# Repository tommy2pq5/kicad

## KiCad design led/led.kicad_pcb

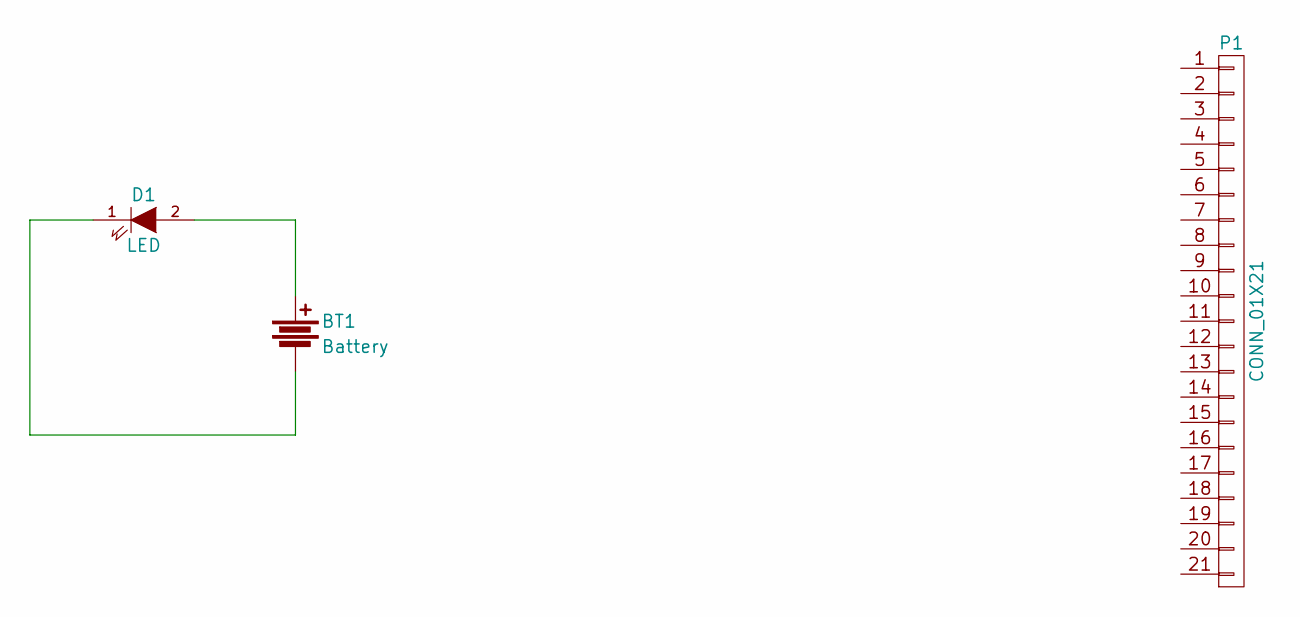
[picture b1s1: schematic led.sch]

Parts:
BT1: Battery; Pin_Header_Straight_2x01_Pitch2.54mm
D1: LED; LED_D5.0mm
P1: CONN_01X21; Pin_Header_Straight_1x21_Pitch2.54mm

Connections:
unnamed: BT1.1, D1.2 (A)
unnamed: BT1.2, D1.1 (K)

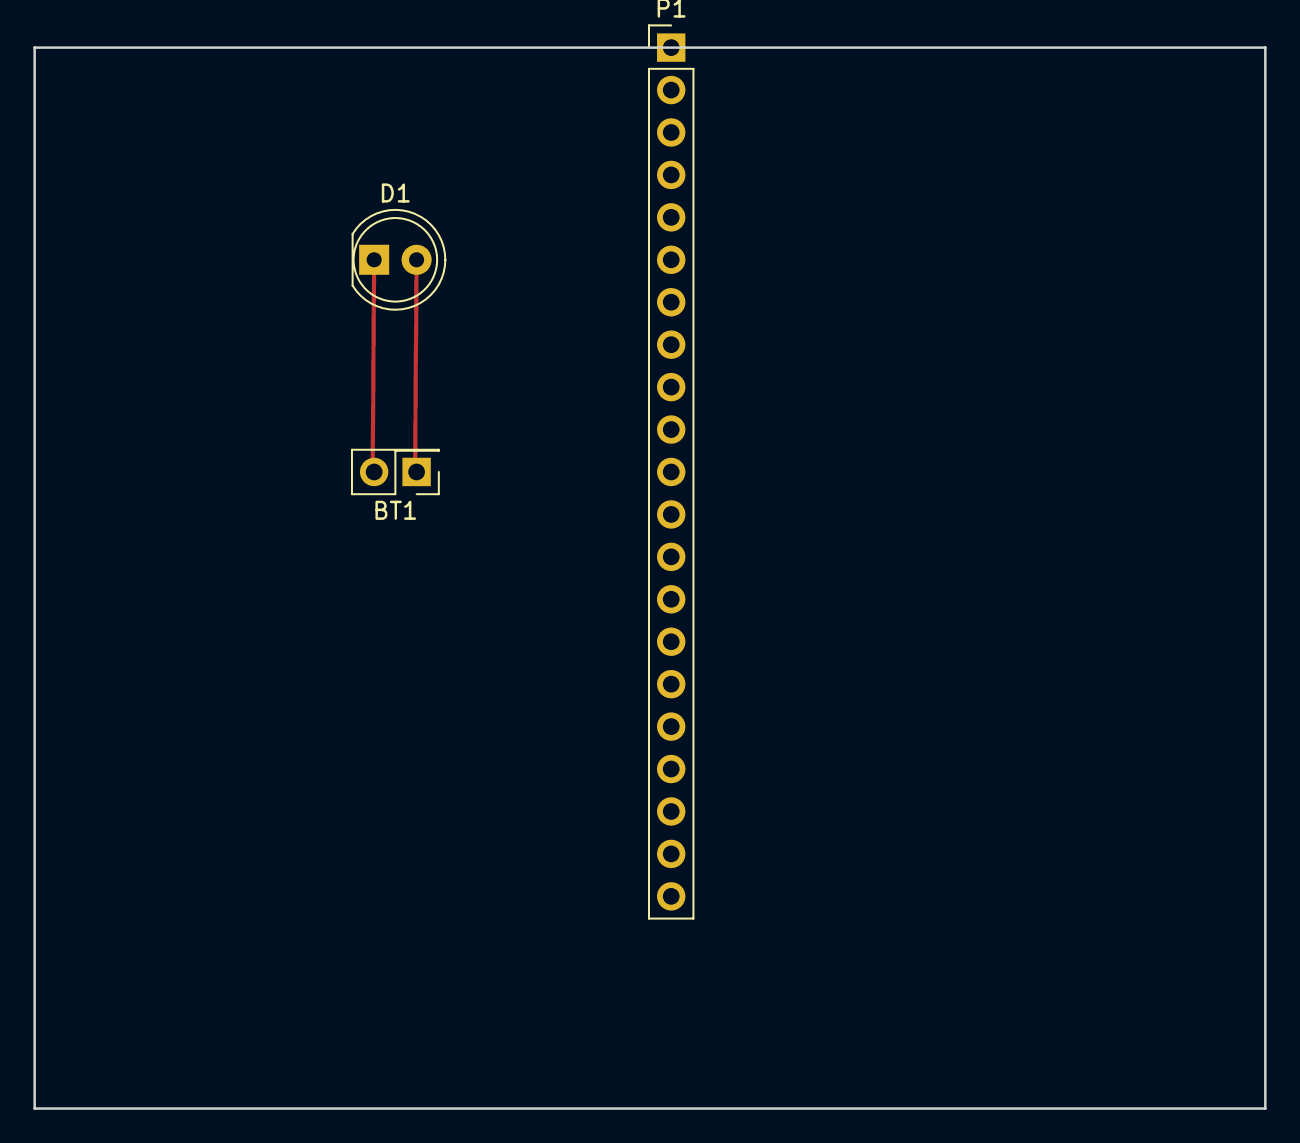
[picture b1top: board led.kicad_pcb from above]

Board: 2 copper layers, 73.7 x 63.5 mm, 3 parts (0 on the bottom side), 2 nets.

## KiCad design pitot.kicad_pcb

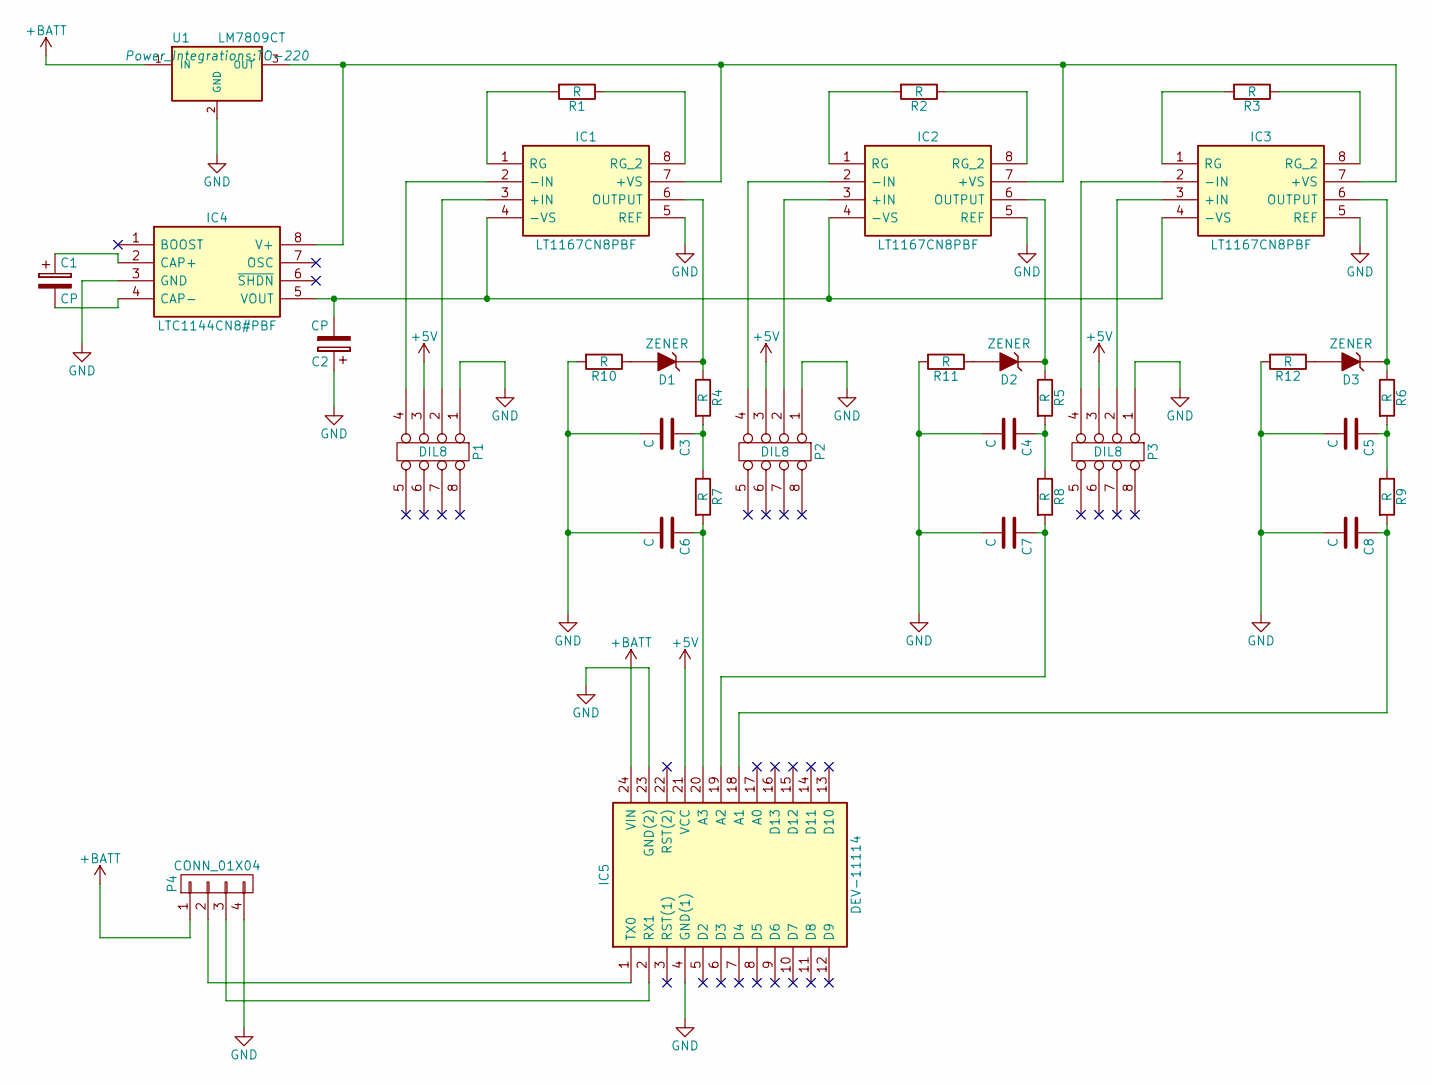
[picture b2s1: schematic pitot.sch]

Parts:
C1, C2: CP; CP_Axial_L10.0mm_D4.5mm_P15.00mm_Horizontal
C3, C4, C5, C6, C7, C8: C; C_Disc_D3.0mm_W1.6mm_P2.50mm
D1, D2, D3: ZENER; D3
IC1, IC2, IC3: LT1167CN8PBF; DIP-8_W7.62mm; Manufacturer_Part_Number LT1167CN8PBF
IC4: LTC1144CN8#PBF; DIP-8_W7.62mm; Manufacturer_Part_Number LTC1144CN8#PBF
IC5: DEV-11114; DIP-24_W7.62mm; Manufacturer_Part_Number DEV-11114
P1, P2, P3: DIL8; DIP-8_W7.62mm
P4: CONN_01X04; Grove_1x04
R1, R2, R3, R4, R5, R6, R7, R8, R9: R; R_Axial_DIN0204_L3.6mm_D1.6mm_P1.90mm_Vertical
R10, R11, R12: R; R_Axial_DIN0204_L3.6mm_D1.6mm_P5.08mm_Horizontal
U1: LM7809CT; TO-220

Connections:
+5V: IC5.21 (VCC), P1.3, P2.3, P3.3
unnamed: C1.1, IC4.2 (CAP+)
unnamed: C1.2, IC4.4 (CAP-)
unnamed: C2.2, IC1.4 (-VS), IC2.4 (-VS), IC3.4 (-VS), IC4.5 (VOUT)
unnamed: C3.1, R4.2, R7.1
unnamed: C4.1, R5.2, R8.1
unnamed: C5.1, R6.2, R9.1
unnamed: C6.1, IC5.20 (A3), R7.2
unnamed: C7.1, IC5.19 (A2), R8.2
unnamed: C8.1, IC5.18 (A1), R9.2
unnamed: D1.1 (K), IC1.6 (OUTPUT), R4.1
unnamed: D1.2 (A), R10.1
unnamed: D2.1 (K), IC2.6 (OUTPUT), R5.1
unnamed: D2.2 (A), R11.1
unnamed: D3.1 (K), IC3.6 (OUTPUT), R6.1
unnamed: D3.2 (A), R12.1
unnamed: IC1.1 (RG), R1.2
unnamed: IC1.2 (-IN), P1.4
unnamed: IC1.3 (+IN), P1.2
unnamed: IC1.7 (+VS), IC2.7 (+VS), IC3.7 (+VS), IC4.8 (V+), U1.3 (OUT)
unnamed: IC1.8 (RG_2), R1.1
unnamed: IC2.1 (RG), R2.2
unnamed: IC2.2 (-IN), P2.4
unnamed: IC2.3 (+IN), P2.2
unnamed: IC2.8 (RG_2), R2.1
unnamed: IC3.1 (RG), R3.2
unnamed: IC3.2 (-IN), P3.4
unnamed: IC3.3 (+IN), P3.2
unnamed: IC3.8 (RG_2), R3.1
unnamed: IC5.1 (TX0), P4.2
unnamed: IC5.2 (RX1), P4.3

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
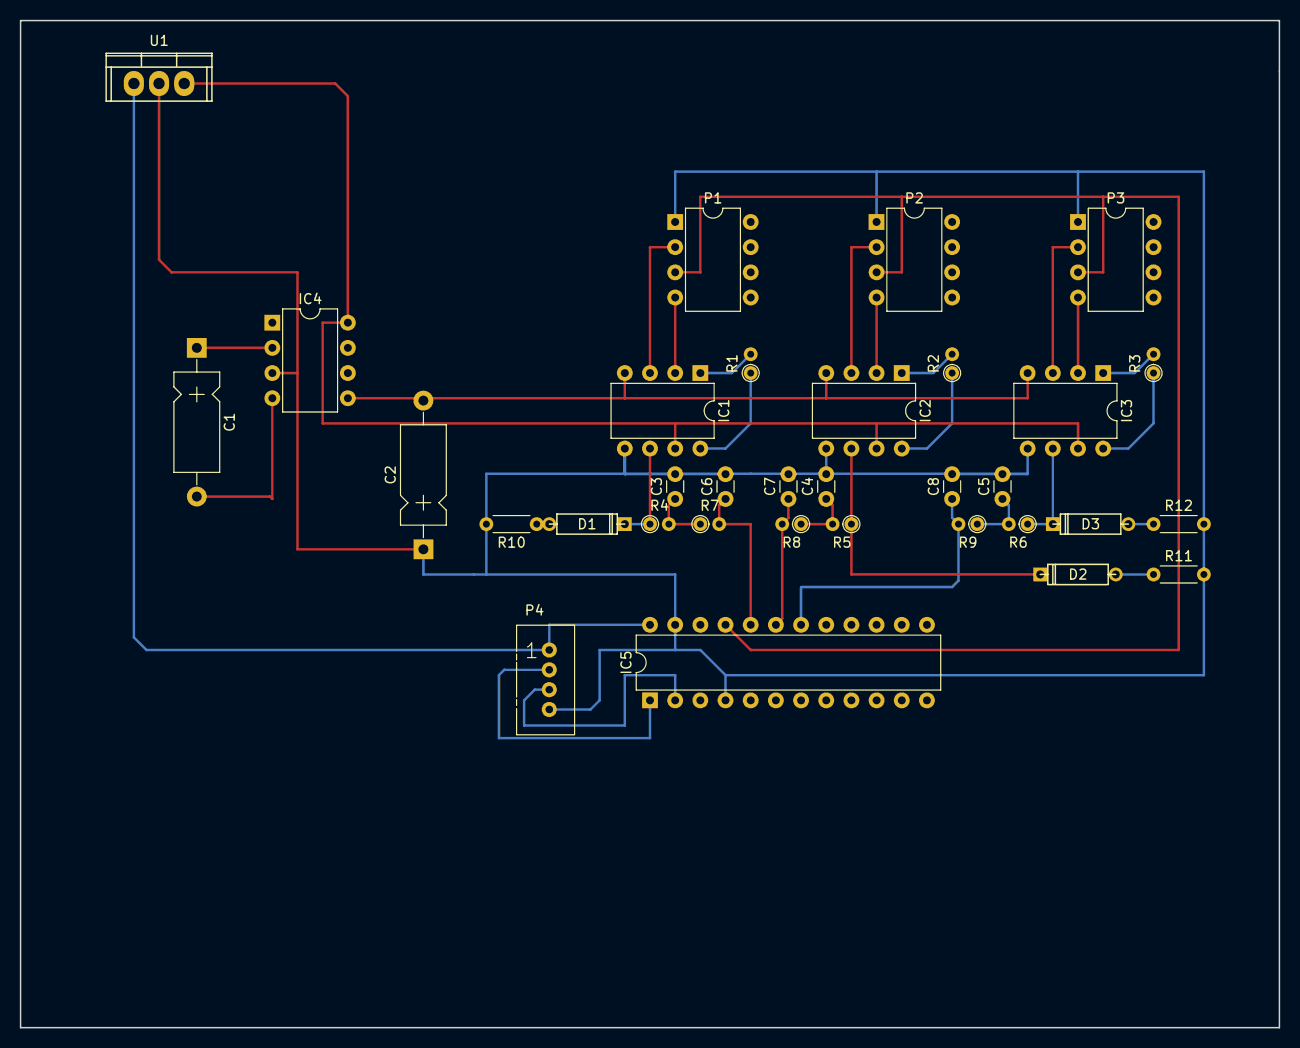
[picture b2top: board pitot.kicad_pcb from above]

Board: 2 copper layers, 127.0 x 101.6 mm, 33 parts (0 on the bottom side), 33 nets.

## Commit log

2017-03-31 prov. pcb layout
2017-03-31 size adj
2017-04-02 add ZD and LPF
2017-04-02 mod pcb layout
2017-04-05 mkdir led AND pitot
